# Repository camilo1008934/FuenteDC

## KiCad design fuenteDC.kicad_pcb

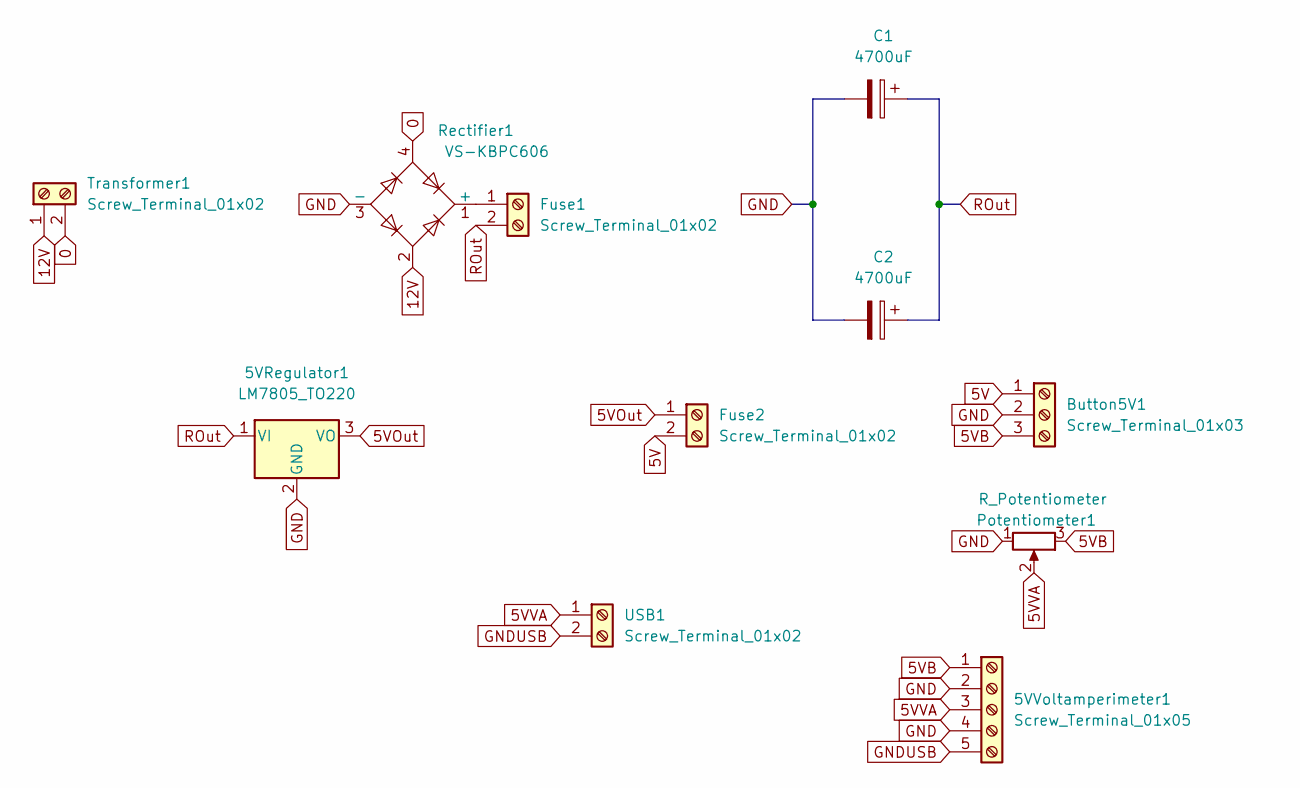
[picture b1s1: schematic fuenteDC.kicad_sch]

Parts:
5VRegulator1: LM7805_TO220; TO-220-3_Vertical
5VVoltamperimeter1: Screw_Terminal_01x05; TerminalBlock_bornier-5_P5.08mm
Button5V1: Screw_Terminal_01x03; TerminalBlock_bornier-3_P5.08mm
C1, C2: 4700uF; CP_Radial_D18.0mm_P7.50mm
Fuse1, Fuse2: Screw_Terminal_01x02; TerminalBlock_bornier-2_P5.08mm
Potentiometer1: R_Potentiometer; TerminalBlock_bornier-3_P5.08mm
Rectifier1: VS-KBPC606; Diode_Bridge_Vishay_KBPC6
Transformer1: Screw_Terminal_01x02; TerminalBlock_bornier-2_P5.08mm
USB1: Screw_Terminal_01x02; TerminalBlock_bornier-2_P5.08mm

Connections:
0: Rectifier1.4, Transformer1.2
5V: Button5V1.1, Fuse2.2
5VB: 5VVoltamperimeter1.1, Button5V1.3, Potentiometer1.3 (V)
5VOut: 5VRegulator1.3 (VO), Fuse2.1
5VVA: 5VVoltamperimeter1.3, Potentiometer1.2, USB1.1
12V: Rectifier1.2, Transformer1.1
GND: 5VRegulator1.2 (GND), 5VVoltamperimeter1.2, 5VVoltamperimeter1.4, Button5V1.2, C1.2, C2.2, Potentiometer1.1 (GND), Rectifier1.3 (-)
GNDUSB: 5VVoltamperimeter1.5, USB1.2
unnamed: Fuse1.1, Rectifier1.1 (+)
ROut: 5VRegulator1.1 (VI), C1.1, C2.1, Fuse1.2

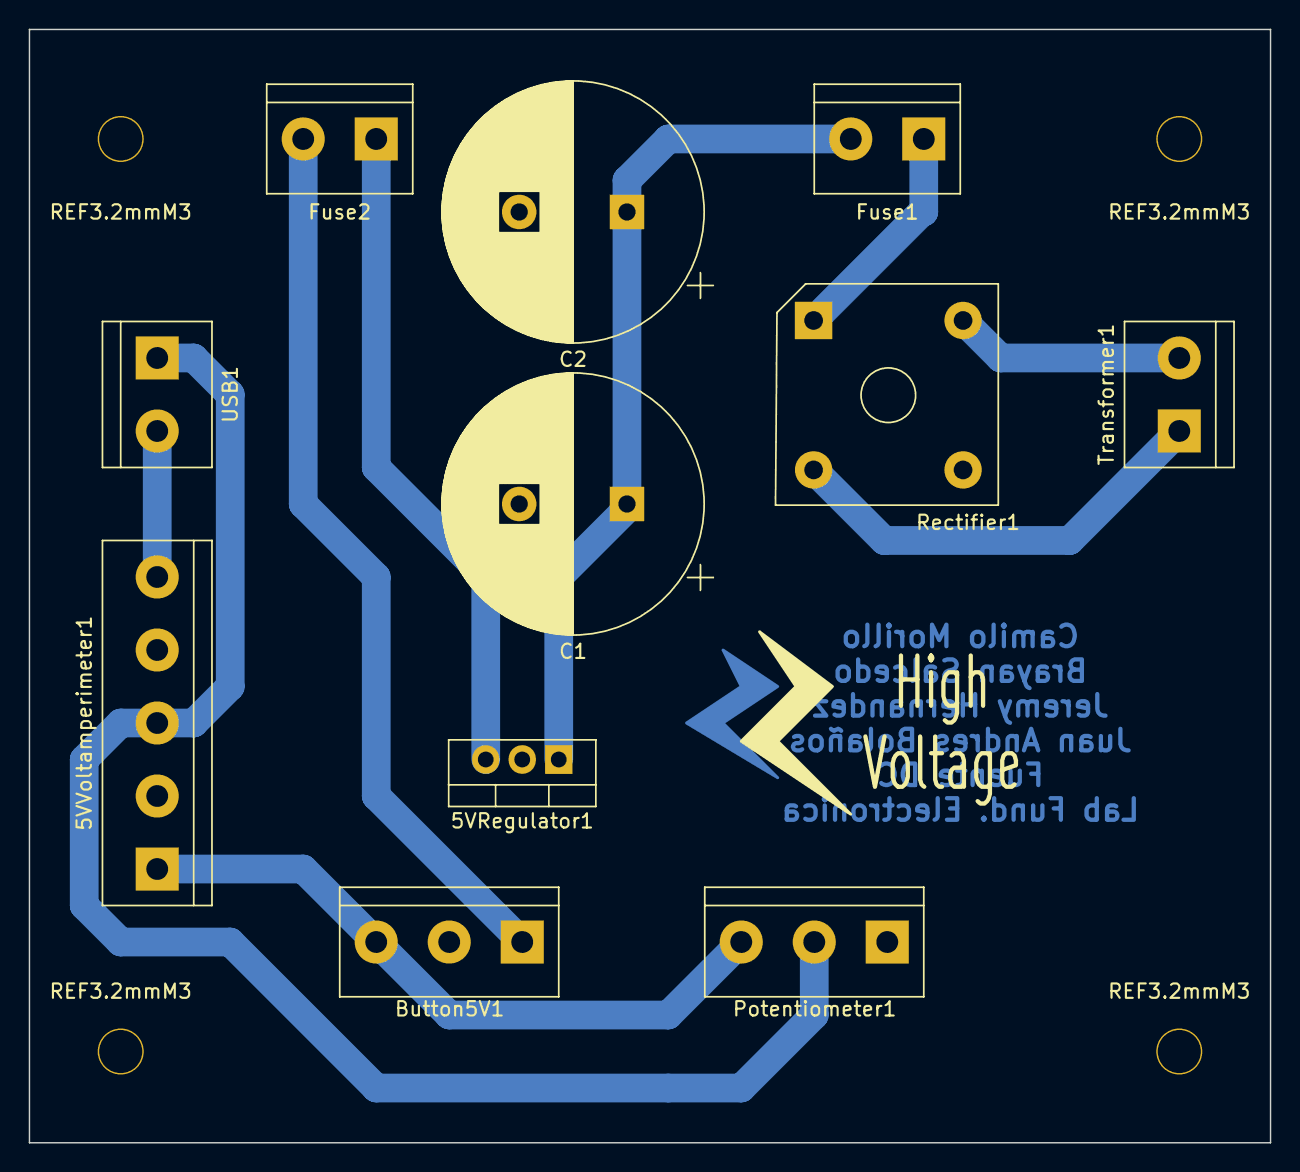
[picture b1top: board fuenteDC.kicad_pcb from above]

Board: 2 copper layers, 86.4 x 77.5 mm, 15 parts (0 on the bottom side), 10 nets.

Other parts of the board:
REF3.2mmM3, REF3.2mmM3#2, REF3.2mmM3#3, REF3.2mmM3#4: MountingHole_3.2mm_M3

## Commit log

2022-10-12 update pcb
